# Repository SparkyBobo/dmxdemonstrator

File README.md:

# DMX Demonstrator

## Background

When I was in grad school, I was challenged by my technical theater professor to create a device to demonstrate DMX. What we devised was a transmitter receiver pair with 4 controls and 4 dimmers and the pair was linked by a three-wire cable. The transmitter had a fixed clock that could run at reasonable fast, xxkHz, and a variable clock that could be adjusted down to 0.5 hZ. By switching back and forth, you could toggle between "real-time" updates and a slow pace that can be used to see each bit on the wire. We then built a lecture around how the data was digitized, serialized, de-serialized, and converted back to analog to control the dimmers.

The device was built and did function even though it failed to follow a number of best engineering practices. At that time, we didn't have [GitHub](https://github.com/) and [Tindie](https://www.tindie.com/) so sharing the project was by word-of-mouth and email; yes, we did have [email](https://en.wikipedia.org/wiki/Email). Only one other group considered building a replica but alas they never did. The device was built only once and transported to a USITT conference in Las Vegas, where the EPROM failed and we had nothing to show except a presentation. Only a handful of students at my school ever got to see it function.

That was 25 years ago. For it's anniversary, I've decided to revive the project and build 2 new implementations. The first is based on Arduino for a cheap but functional version of the project that is unlikely to fail or break the bank. The second is an updated recreation of the original using today's available hardware but without deviating from the original TTL-based design, i.e. no microprocessors or microcontrollers. I'll admit this last one is really just for me because I love designing electronics, drawing schematics, laying out PCBs, and assembling electronics.

## Hardware

In the hardware folder, you'll find a series of designs:

- transmitter - An arduino-based transmitter.
- receiver - An arduino-based receiver.
- control-pro - A controller built to work with either transmitter or transmitter-pro.
- constant voltage display driver - An external large-format display for data and clock signals.

## Firmware/Software

As you would expect, the Arduino-based version is implemented mostly in software. The Sketch files for both transmitter and receiver are in the software folder and ready to upload to an Arduino UNO R3. The sketch and hardware will likely work with any Arduino-compatible board.

## Monitoring

All informational output is sent to via the serial port for easy display on a computer. However, the clock and serial data are displayed via LEDs to visualize the serial data.

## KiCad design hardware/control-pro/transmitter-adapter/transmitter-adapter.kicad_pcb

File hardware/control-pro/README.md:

# DMX Demonstrator Control Pro  (DMX-CP*)

## Overview

The Control Pro is built to work with either transmitter or transmitter-retro. When used with an Arduino, an additional board, the Transmitter IO Interface (DMX-TX2), is required to connect the Control Pro to the Arduino. The transmitter software automatically detects whether DMX-TX1, the standard transmitter, or DMX-TX2, the Transmitter IO Interface, is connected.

The Control Pro is designed so that a series of components are sandwiched between 2 circuit boards. As a result, the heights of the components are fairly sensitive in order to make things line up nicely. The DMX-CPDB and DMX-CPCB boards contains all the parts and are the bottom of the sandwich, the DMX-CPDF and DMX-CPCB are the faceplate, i.e. the tops of the sandwich. If you are wondering why there are 4 total boards, see _PCB->Quality vs Price_ below.

## Online parts list

For a complete list of parts, see:

- [Clock Control Bill of materials](clock-control/clock-control.bom.md), [Clock Control Parts](clock-control/clock-control.parts.md)
- [Dimmer Control Bill of materials](dimmer-control/dimmer-control.bom.md), [Dimmer Control Parts](dimmer-control/dimmer-control.parts.md)
- [Clock Faceplate Bill of materials](clock-faceplate/clock-faceplate.bom.md), [Clock Faceplate Parts](clock-faceplate/clock-faceplate.parts.md)
- [Dimmer Faceplate Bill of materials](dimmer-faceplate/dimmer-faceplate.bom.md), [Dimmer Faceplate Parts](dimmer-faceplate/dimmer-faceplate.parts.md)
- [Transmitter Adapter Bill of materials](transmitter-adapter/transmitter-adapter.bom.md), [Transmitter Adapter Parts](transmitter-adapter/transmitter-adapter.parts.md)

You can also buy some of the parts for the Control Pro online from a Wishlist:

- Sparkfun: [Common](https://www.sparkfun.com/wish_lists/160406), [DMX-CP*](https://www.sparkfun.com/wish_lists/160543)
- Adafruit: [Common](http://www.adafruit.com/wishlists/589832), [DMX-CP*](http://www.adafruit.com/wishlists/590129)

Sparkfun's rainbow LED pack only include 2 sets of color so if you are building more than 2 transmitters or receivers, make sure to buy 1 pack for every 2 transmitters/receivers. Adafruit's LED pack includes 5 sets of each color.

## PCB

You can order the PCBs from [OHS Park](https://oshpark.com/):

- [Clock Control: DMX-CPCB, Rev 1.3](https://oshpark.com/shared_projects/llBuRZd8)
- [Clock Faceplate: DMX-CPCF, Rev 1.3](https://oshpark.com/shared_projects/S9LARHyr)
- [Dimmer Control: DMX-CPDB, Rev 1.3](https://oshpark.com/shared_projects/O76YiRT8)
- [Dimmer Faceplate: DMX-CPDF, Rev 1.3](https://oshpark.com/shared_projects/bZqKigQF)
- [Transmitter Adapter: DMX-CPAD, Rev 1.3](https://oshpark.com/shared_projects/xCkM6ON9)

You can read more about ordering pcbs [here](../pcb.md).

## Assembly Notes

The Control Pro is designed so that a series of components are sandwiched between 2 circuit boards. As a result, the heights of the components are fairly sensitive in order to make things line up nicely. Here are the parts for which I designed. The DMX-CPDB and DMX-CPCB boards contains all the parts and are the bottom of the sandwich, the DMX-CPDF and DMX-CPCB are the faceplate, i.e. the tops of the sandwich. If you are wondering why there are 4 total boards, [read this](../pcb.md).

### Slider Potentiometers

Getting a potentiometer and knob combo that would work with the rest of the components was probably the hardest part of part selection.
I had initially ordered some 60mm 10k sliders from SparkFun with matching knobs and they measures about 25mm from the bottom of the
part to the bottom of the knob, which is way too tall for the other components! I landed on a combination of Bourns PTA Series
sliders with an knob available from Sparkfun (and others). During this process, I opted for a 45mm travel to keep the board smaller/cheaper
while still offering good mechanical resolution. The specific parts I designed for are:

- Dimmer Sliders: Bournes PTA4543-2015DPB103, quantity 4:

  - [Data sheet](https://www.mouser.com/datasheet/2/54/pta-778345.pdf)
  - [Digikey PTA4543-2015DPB103-ND](https://www.digikey.com/products/en?keywords=PTA4543-2015DPB103-ND)
  - [Mouser 652-PTA45432015DPB10](https://www.mouser.com/ProductDetail/Bourns/PTA4543-2015DPB103?qs=U%2FacTlguYxbmwS%2FtylIWJw%3D%3D)

- Knobs: Eagle 450-3051, quantity 4:

  - [Datasheet](https://www.mouser.com/datasheet/2/209/EPD-200140-1171100.pdf)
  - [Mouser 450-3051](https://www.mouser.com/ProductDetail/Eagle-Plastic-Devices/450-3051?qs=hTs5c5NaUrTeABpuQnP9ug%3D%3D)
  - [Sparkfun COM-09120](https://www.sparkfun.com/products/9120) - Included in online parts list

### Toggle Switches

Just about any miniature toggle switch will do, many manufacturers make a switch in a similar size. I specifically used the E-Switch Series 100 Miniature Toggle Switches, specifically:

- Clock Speed: E-Switch 100DP3T1B1M1QEH, quantity 1:

  - [Datasheet](https://sten-eswitch-13110800-production.s3.amazonaws.com/system/asset/product_line/data_sheet/129/100.pdf)
  - [Digikey EG2413-ND](https://www.digikey.com/products/en?keywords=100DP3T1B1M1QEH)
  - [Mouser 612-100-H1111](https://www.mouser.com/ProductDetail/E-Switch/100DP3T1B1M1QEH?qs=g8hxKYs5b3yy1L1GZVrx5w%3D%3D)

- Clock Step: E-Switch 100SP2T1B1M1QEH, quantity 1:

  - [Datasheet](https://sten-eswitch-13110800-production.s3.amazonaws.com/system/asset/product_line/data_sheet/129/100.pdf)
  - [Digikey EG2373-ND](https://www.digikey.com/product-detail/en/e-switch/100SP2T1B1M1QEH/EG2373-ND/378842)
  - [Mouser 612-100-B1111](https://www.mouser.com/ProductDetail/E-Switch/100SP2T1B1M1QEH?qs=HKd%2Fp3M7KlWCZ%252BGqDexPKQ%3D%3D)

### Rotary Potentiometer

With the toggle and sliders determining the basic component height, I searched for a rotary potentiometer to fit the requirements and once again found a Bournes product. It has a 6mm "D"/flattened shaft so just about any 6mm flattened shaft knob will work but something with a set screw will help secure it. I did not find a great choice at Digikey or Mouser but Amazon and EBay has a ton of choices, designed for use with musical instruments.

Sparkfun offers a potentiometer and knob that make an excellent choice. The knob even [goes to 11](https://en.wikipedia.org/wiki/Up_to_eleven). The Sparkfun part is not a Bournes PTV09A-4030F-B103 but it's the same physical size and resistance.

Specifically:

- Clock Speed Control: Bournes PTV09A-4030F-B103, quantity 1:

  - [Datasheet](https://www.bourns.com/docs/Product-Datasheets/PTV09.pdf)
  - [Digikey 118-PTV09A-4030F-B103-ND](https://www.digikey.com/en/products/detail/bourns-inc/PTV09A-4030F-B103/3820581)
  - [Mouser 652-PTV09A-4030FB103](https://www.mouser.com/ProductDetail/Bourns/PTV09A-4030F-B103?qs=Zq5ylnUbLm4pfFuWlwC80Q%3D%3D)
  - [Sparkfun COM-09288](https://www.sparkfun.com/products/9288) - Included in online parts list

- Knob, quantity 1:

  - [Sparkfun COM-11951](https://www.sparkfun.com/products/11951) - Included in online parts list
  - [Adafruit 5527](https://www.adafruit.com/product/5527) - Included in online parts list

### LEDs and Spacers

Luckily most LEDs have leads long enough to make it from the bottom to top board so nothing special is needed here, just make sure to have 17.5mm of lead length. Most LEDs have a voltage and current range near 2v and 10ma and the design will accommodate variances easily.

I like the [Sparkfun rainbow LED Kit](https://www.sparkfun.com/products/12903) which gives you 2 each of 6 colors, letting you match colors for dimmers 1-4, data and clock on both the transmitter and receiver without re-using colors. This LED kit is included in the common parts list. However, they will need a bit of added stability, which is where an LED spacer is needed. Something between 16mm and 17mm will work fine. Here's a suitable one:

- LED: T1 3/4 or 5mm Led in various colors, quantity 1:

  - [Sparkfun rainbow LED Kit](https://www.sparkfun.com/products/12903) - Included in common online parts list
  - [Adafruit Multicolor LED Kit](https://www.adafruit.com/product/4203) - Included in common online parts list

- LED Spacer: Würth 705820170, quantity 6:

  - [Data sheet](https://www.we-online.de/katalog/datasheet/705820xxx_overview.pdf)
  - [Digikey 732-11617-ND](https://www.digikey.com/product-detail/en/w%C3%BCrth-elektronik/705820170/732-11617-ND/7681962)
  - [Mouser 710-705820170](https://www.mouser.com/ProductDetail/Wurth-Elektronik/705820170?qs=wr8lucFkNMUaK6Cwpwjx5Q%3D%3D)

### Cable and Connector

To connect the controller to the transmitter, you'll need some cables and connectors. Ribbon cable makes a nice choice for this and you can find pre-made ribbon cable assemblies on Amazon and EBay easily. I've designed for a 16 pin cable. I recommend shrouded headers for connecting to PCBs and it ensures you don't plug the cable in backwards. Here are some suitable headers:

- Header, horizontal: Würth Elektronik 61201621721, quantity 5:

  - [Datasheet](https://www.we-online.com/components/products/datasheet/61201621721.pdf)
  - [Digikey 732-2099-ND](https://www.digikey.com/en/products/detail/w%C3%BCrth-elektronik/61201621721/2060595)
  - [Mouser 710-61201621721](https://www.mouser.com/ProductDetail/Wurth-Elektronik/61201621721?qs=ZtY9WdtwX56ShT0tAQh3qw%3D%3D)

- Cable, quantity 2:

  - [Amazon: Antrader 30CM 16-Pin IDC Connector Flat Ribbon Cable](https://smile.amazon.com/dp/B07FZWH9S6/ref=cm_sw_em_r_mt_dp_n0-BFbMSE9MJX )

### Standoff and Feet

Finally, you'll need some standoffs to hold the boards together and some feet to avoid the bottom PCB from dragging across the table. You can adjust the screw size and add some washers or plexiglass if you like to create a smooth bottom surface. The standoffs should be 18mm in length and the boards are designed for an M3 screw. Amazon and EBay offer tons of options. I even found [purple ones on EBay](https://www.ebay.com/itm/M3-Aluminum-Alloy-Female-Hex-Hexagon-Threaded-Bush-Sleeve-Standoff-Pillar-Spacer/174350100853?ssPageName=STRK%3AMEBIDX%3AIT&var=473550930125&_trksid=p2060353.m1438.l2649).

- Standoff: Keystone 24476/24446/25531 (M3, 18mm length), quantity 4:

  - [Digikey 36-24446-ND, aluminum](https://www.digikey.com/product-detail/en/keystone-electronics/24446/36-24446-ND/1532945)
  - [Mouser 534-24436, aluminum](https://www.mouser.com/ProductDetail/Keystone-Electronics/24436?qs=UWqYQ%2F2cZWv7%252B7DoeljlhQ%3D%3D)
  - [Ebay M3 Aluminum Alloy Red, Blue, Purple, Black, Gold, Silver](https://www.ebay.com/itm/M3-Aluminum-Alloy-Female-Hex-Hexagon-Threaded-Bush-Sleeve-Standoff-Pillar-Spacer/174350100853?ssPageName=STRK%3AMEBIDX%3AIT&var=473550930125&_trksid=p2060353.m1438.l2649)

### Passive components

The Control Pro has a few passive listed on the schematic and are included in the common parts lists:

- Sparkfun: [Common](https://www.sparkfun.com/wish_lists/160406)
- Adafruit: [Common](http://www.adafruit.com/wishlists/589832)

## Version History

### Rev 1.3

- Add copper pours to both faceplates
- No changes to control boards.
- Added transmitter adapter.

### Rev 1.2

#### DMX-CPC*

- Split clock controls out to its own PCB
- Added 2nd 16 pin connector to daisy chain with DMX-CPD*.
- Switched to horizontal 16 pin connectors since vertical was too tall with a cable plugged in
- Swapped the clock speed and step switches to match the order on the TX1
- Swapped the data and clock LEDs to match the order on the TX1

#### DMX-CPD*

- Split dimmer controls out to its own PCB
- Added 2nd 16 pin connector to daisy chain with DMX-CPC*.
- Switched to horizontal 16 pin connectors since vertical was too tall with a cable plugged in

### Rev 1.1

#### DMX-CPB

- Added rounded corners.

#### DMX-CPF

- Removed copper from 3rd slider slot by enlarging slot width.
- Added rounded corners.

### Rev 1.0

- Initial draft, all boards.

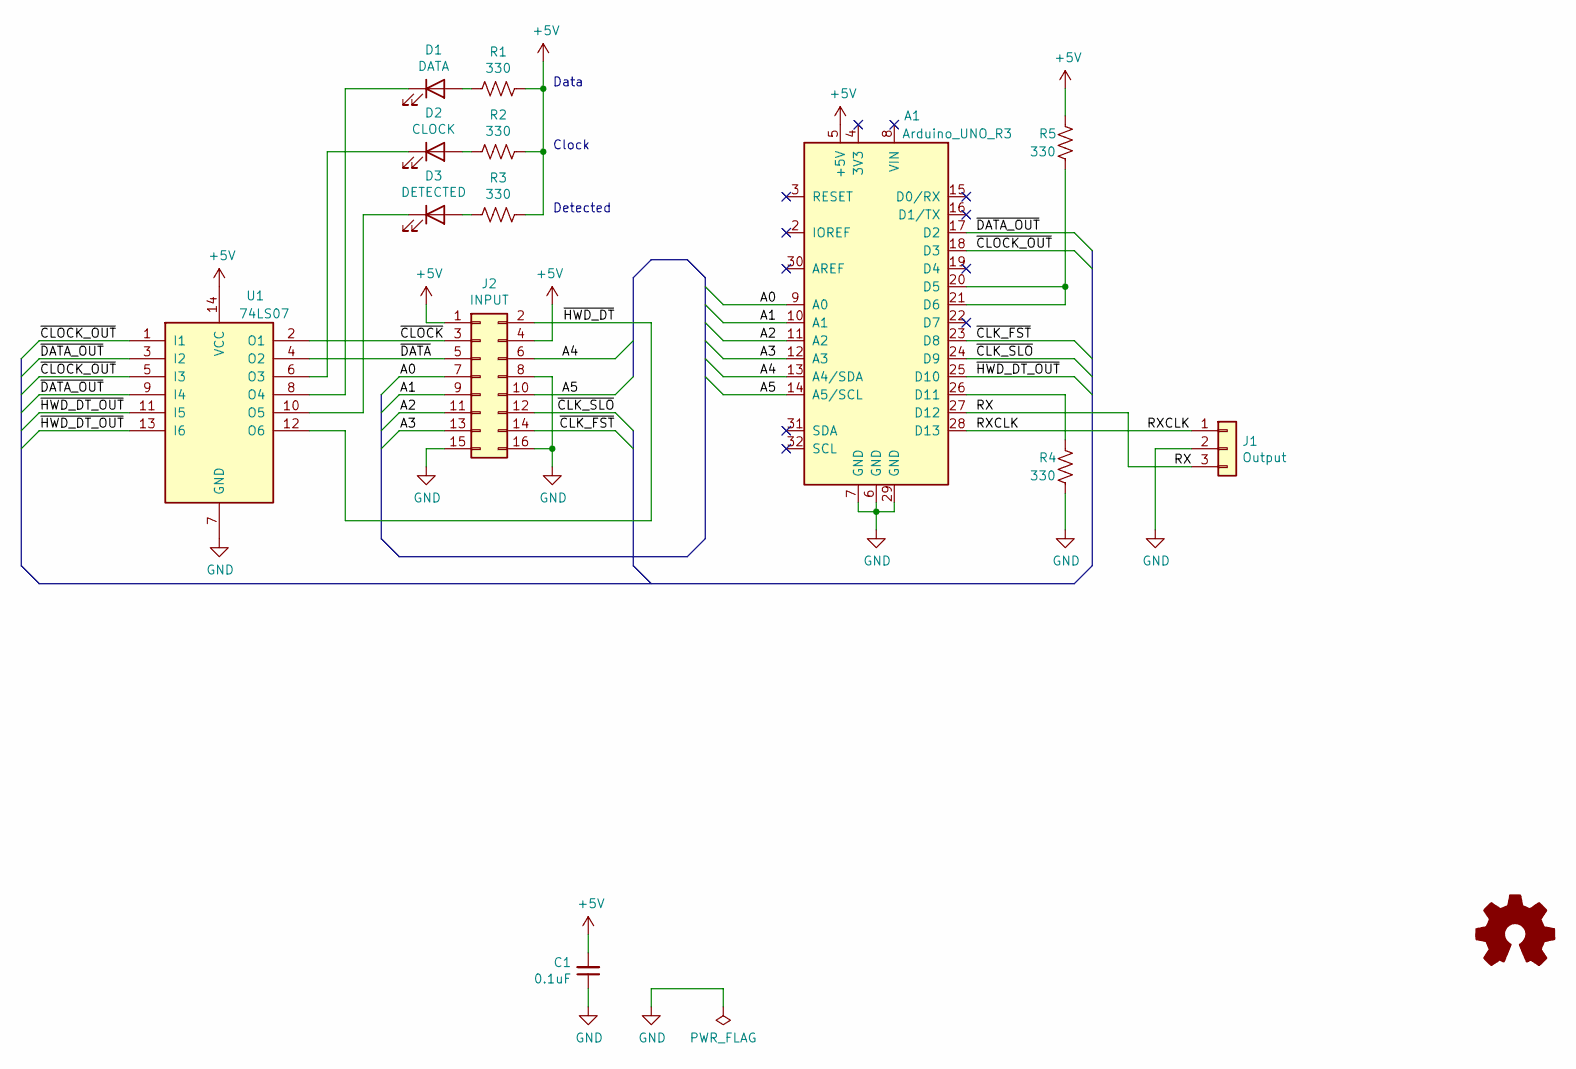
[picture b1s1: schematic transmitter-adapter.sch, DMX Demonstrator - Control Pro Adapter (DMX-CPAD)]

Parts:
A1: Arduino_UNO_R3; ARDUINO_R3_NO_HOLES; PartId A_ARDUINO,H_ARDUINO
C1: 0.1uF; C_Disc_D3.0mm_W1.6mm_P2.50mm; PartId C_DECOUPLE
D1: DATA; LED_D5.0mm; PartId LED_GRN
D2: CLOCK; LED_D5.0mm; PartId LED_RED
D3: DETECTED; LED_D5.0mm; PartId LED_RED
J1: Output; PinHeader_1x03_P2.54mm_Horizontal; PartId H_1x3_RA
J2: INPUT; IDC-Header_2x08_P2.54mm_Horizontal; PartId H_CPRO_RA
R1, R2, R3, R4, R5: 330; R_Axial_DIN0207_L6.3mm_D2.5mm_P10.16mm_Horizontal; PartId R_LED
U1: 74LS07; DIP-14_W7.62mm; PartId U_74LS07

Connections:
+5V: A1.5 (+5V), C1.2, J2.1, J2.4, R1.1, R2.1, R3.1, R5.1, U1.14 (VCC)
/A0: A1.9 (A0), J2.7
/A1: A1.10 (A1), J2.9
/A2: A1.11 (A2), J2.11
/A3: A1.12 (A3), J2.13
/A4: A1.13 (A4/SDA), J2.6
/A5: A1.14 (A5/SCL), J2.10
/RX: A1.27 (D12), J1.3
/RXCLK: A1.28 (D13), J1.1
/~CLK_FST: A1.23 (D8), J2.14
/~CLK_SLO: A1.24 (D9), J2.12
/~CLOCK: J2.3, U1.2 (O1)
/~CLOCK_OUT: A1.18 (D3), U1.1 (I1), U1.5 (I3)
/~DATA: J2.5, U1.4 (O2)
/~DATA_OUT: A1.17 (D2), U1.3 (I2), U1.9 (I4)
/~HWD_DT: J2.2, U1.12 (O6)
/~HWD_DT_OUT: A1.25 (D10), U1.11 (I5), U1.13 (I6)
GND: A1.6 (GND), A1.7 (GND), A1.29 (GND), C1.1, J1.2, J2.8, J2.15, J2.16, R4.2, U1.7 (GND)
unnamed: A1.20 (D5), A1.21 (D6), R5.2
unnamed: A1.26 (D11), R4.1
unnamed: D1.1 (K), U1.8 (O4)
unnamed: D1.2 (A), R1.2
unnamed: D2.1 (K), U1.6 (O3)
unnamed: D2.2 (A), R2.2
unnamed: D3.1 (K), U1.10 (O5)
unnamed: D3.2 (A), R3.2

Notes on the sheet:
Clock
Data
Detected

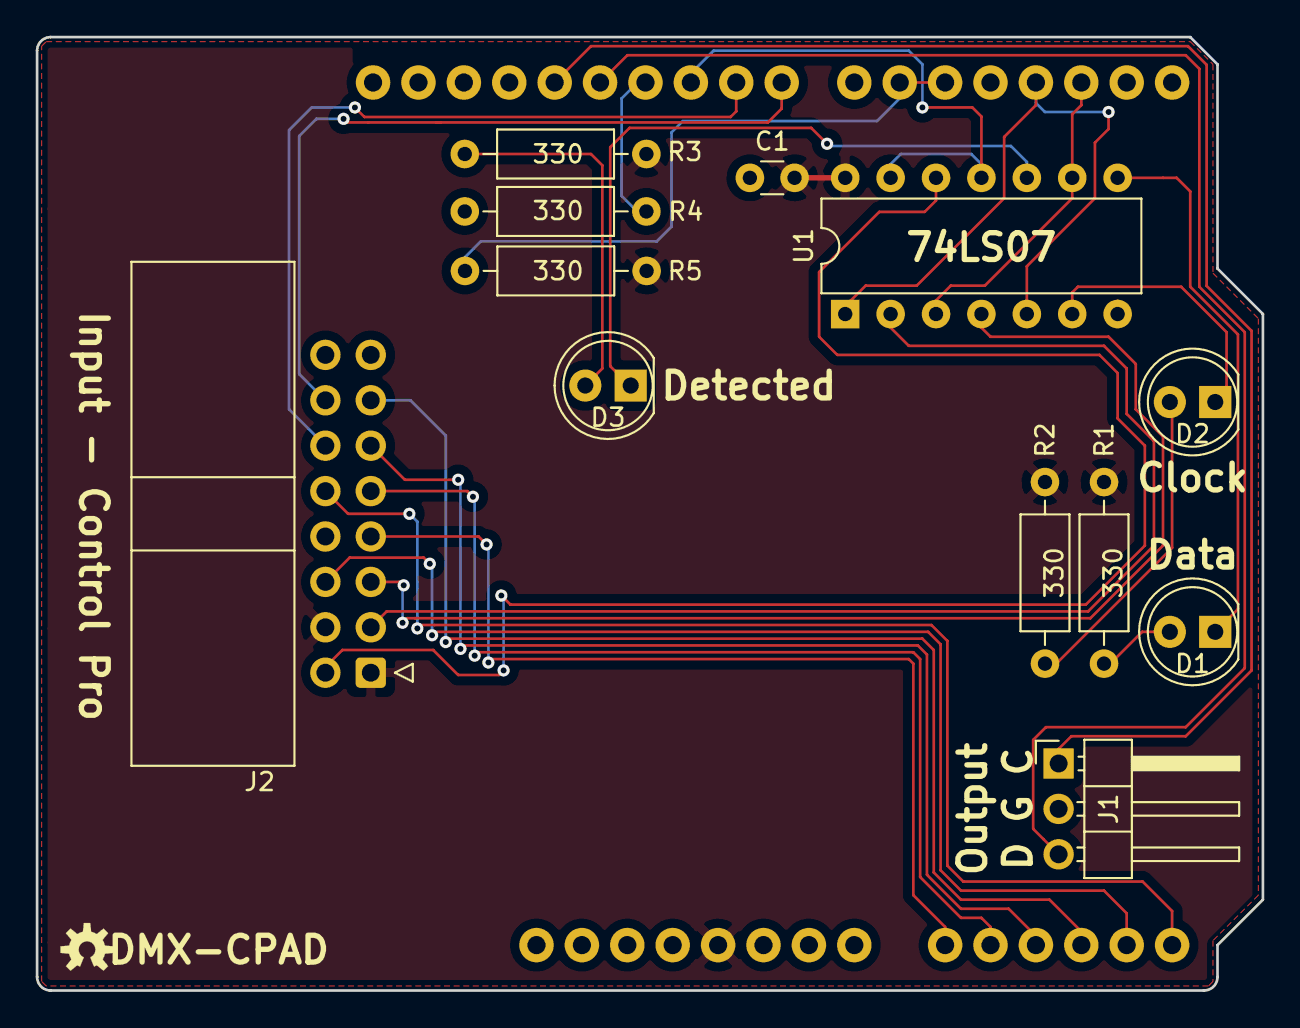
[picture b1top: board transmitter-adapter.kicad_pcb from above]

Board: 2 copper layers, 68.6 x 53.3 mm, 13 parts (0 on the bottom side), 26 nets.

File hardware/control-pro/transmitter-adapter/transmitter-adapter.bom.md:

# Bill Of Materials (BOM)

## Schematic

**Filename:** E:\OpenSource\dmxdemonstrator\hardware\control-pro\transmitter-adapter\transmitter-adapter.sch

**Date Modified:** 5/25/2024 12:26:10 AM

**Kicad Version:** Eeschema (5.1.12)-1

**Component Count:** 13

## Components

Item#|Quantity|Reference|Description|Manufacturer|Part Number|Datasheet|Notes
-----|--------|---------|-----------|------------|-----------|---------|-----
1|1|PCB|Control-Pro Adapter PCB|OHSPark|DMX-CPAD, Rev 1.3||[Order](https://oshpark.com/shared_projects/xCkM6ON9)|
2|1|A1|Arduino UNO/Leonardo|||[Data Sheet](https://www.arduino.cc/en/Main/arduinoBoardUno)|
3|1|A1|Arduino R3 Headers|||[Data Sheet](https://www.arduino.cc/en/Main/arduinoBoardUno)|
4|1|C1|0.1uF||||
5|1|D1|Green LED, 5mm||||
6|1|D2|Red LED, 5mm||||
7|1|D3|Red LED, 5mm||||
8|1|J1|3-pin right-angle header||||
9|1|J2|2x8 shrouded right-angle header|Wurth Elektronik|61201621721|[Data Sheet](https://www.we-online.com/components/products/datasheet/6120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|
10|5|R1, R2, R3, R4, R5|330 ohm||||
11|1|U1|74LS07|Texas Instruments|SN74LS07N|[Data Sheet](https://www.ti.com/lit/gpn/sn74ls07)|
<!--BOMROW-->

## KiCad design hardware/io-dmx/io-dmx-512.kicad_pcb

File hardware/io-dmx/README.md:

# DMX Demonstrator DMX-512 IO Module (DMX-IO1)

## Overview

The DMX-512 IO Module is a stand-alone module which generates or receives a DMX-512 signal, allowing the DMS Demonstrator system to communicate with DMX-512-compatible equipment. It can be used with a Receiver (DMX-RX2) to receive or re-transmit DMX-512. It can also be used with a Transmitter (DMX-TX2) to transmit the data stream to DMX-512.

## Online parts list

For a complete list of parts, see:

- [Bill of materials](io-dmx-512.bom.md)
- [Part lists](io-dmx-512.parts.md)

Sadly, Sparkfun and Adafruit do not offer all of the components required for DMX-512 IO Module. Additionally, Digikey does not carry Neutrik for connecting to the DMX devices. The parts can be purchased from [Mouser](https://www.mouser.com/) or [Newark](https://www.newark.com/). Some parts can be purchased from [SparkFun](https://www.sparkfun.com/) and [Adafruit](https://www.adafruit.com/).

### Required components

- U5, MAX485E

  - [MAX485E Data Sheet](https://www.analog.com/media/en/technical-documentation/data-sheets/MAX1487E-MAX491E.pdf)
  - [Mouser 700-MAX485CPA](https://www.mouser.com/ProductDetail/Analog-Devices-Maxim-Integrated/MAX485CPA%2b?qs=1THa7WoU59FcxPgOoQv70A%3D%3D)
  - [Newark 881Y9485](https://www.newark.com/analog-devices/max485cpa/rs422-rs485-transceiver-2-5mbps/dp/81Y9485?ost=max485cpa)

- C5, 0.1uF

  - [SparkFun 8375](https://www.sparkfun.com/products/8375)
  - [Adafruit 753](https://www.adafruit.com/product/753)
  - [Mouser 80-C320C104K5R7301](https://www.mouser.com/ProductDetail/KEMET/C320C104K5R5TA7301/?qs=cWONFOU2MXytiO%2Fz22pl%252Bg%3D%3D)
  - [Newark 13K6284](https://www.newark.com/kemet/c315c104m5u5ta/capacitor-mlcc-z5u-100nf-50v-radial/dp/39K6432)

- R2, R5, and R7, 470 ohm

  - [Adafruit 2781](https://www.adafruit.com/product/2781)
  - [Mouser 603-CFR-25JT-52-470R](https://www.mouser.com/ProductDetail/Yageo/CFR-25JT-52-470R/?qs=sGAEpiMZZMtlubZbdhIBIFoOGUvNp40adtovOrQ4BzA%3D)
  - [Newark 38K0375](https://www.newark.com/multicomp-pro/mcf-0-25w-470r/carbon-film-resistor-470-ohm-250mw/dp/38K0375)

- J1, 2x7 shrouded right-angle header

  - [Datasheet](https://www.we-online.com/components/products/datasheet/61201421721.pdf)
  - [Mouser 710-61201421721](https://www.mouser.com/ProductDetail/Wurth-Elektronik/61201421721?qs=PhR8RmCirEbQk5OcjPFu0A%3D%3D)
  - [Newark 75AJ1395](https://www.newark.com/wurth-elektronik/612014235221/conn-r-a-header-14pos-2row-2-54mm/dp/75AJ1395)

### DMX Connectors

DMX commonly uses a 5-pin XLR connector. From the [Recommended Practices for DMX-512, 2nd Edition by Adam Bennette](https://tsp.esta.org/tsp/documents/docs/DMX512-A_Guide_(8x10)_ESTA.PDF):

> DMX512-A lines connect with equipment via XLR 5 pin type connectors. A female connector is fitted to a transmitter and a male connector to a receiver.

However, some DMX equipment is equipped 3-pin XLR connectors which does not comply with the USITT spec. That said, the DMX-IO1 supports both XLR-5 and XLR-3 connectors, one male and one female. The design is made for Neutrik connectors (which is not a brand that Digikey carries). There are a few variation of the basic part numbers listed below with different shielding configurations. For instance, Newark only carries the NC3FAH-2, which works fine in place of the NC3FAH.

- XLR, 5-pin male

  - [NC5MAH Datasheet](https://www.neutrik.com/en/product/nc5mah.pdf)
  - [Mouser 568-NC5MAH](https://www.mouser.com/ProductDetail/Neutrik/NC5MAH/?qs=43pPWqpsSNtpdAMzqMXlkw%3D%3D)
  - [Newark 25C4313](https://www.newark.com/neutrik/nc5mah/connector-xlr-audio-plug-5pos/dp/25C4313?ost=nc5mah)

- XLR, 5-pin female

  - [NC5FAH Datasheet](https://www.neutrik.com/en/product/nc5fah.pdf)
  - [Mouser 568-NC5FAH](https://www.mouser.com/ProductDetail/Neutrik/NC5FAH/?qs=JfNPhaIww3Jo8umm7Mfi2w%3D%3D)
  - [Newark 94C1524](https://www.newark.com/neutrik/nc5fah/connector-xlr-receptacle-5-position/dp/94C1524?ost=nc5fah)

- XLR, 3-pin male

  - [NC3MAH Datasheet](https://www.neutrik.com/en/product/nc3mah.pdf)
  - [Mouser 568-NC3MAH](https://www.mouser.com/ProductDetail/Neutrik/NC3MAH/?qs=MO8z%252B%252BLepAHrH1t47qrfbA%3D%3D)
  - [Newark 91F3468](https://www.newark.com/neutrik/nc3mah/connector-xlr-plug-3-position/dp/91F3468?st=nc3mah)

- XLR, 3-pin female

  - [NC3FAH-0 Datasheet](https://www.neutrik.com/en/product/nc3fah-0.pdf)
  - [Mouser 568-NC3FAH](https://www.mouser.com/ProductDetail/Neutrik/NC3FAH/?qs=43pPWqpsSNse2FCN7qQVQw%3D%3D)
  - [Newark 27B4208](https://www.newark.com/neutrik/nc3fah2/connector-xlr-audio-rcpt-3pos/dp/27B4208)

### DMX Termination

From the [Recommended Practices...](https://tsp.esta.org/tsp/documents/docs/DMX512-A_Guide_(8x10)_ESTA.PDF):

> Incorrect or missing termination is probably the single most common reason for faulty DMX512-A systems. The terminator is a resistor fitted between the two data lines (pins 2 & 3 of an XLR 5 pin connector) at the end of the cable furthest from the transmitter.

The DMX-IO1 includes a part to terminate the DMX-512 line. To add termination, populate R1 with a 120 ohm resistor. Add SW1 to make termination selectable or solder a jumper between the two round pads for permanent termination.

- R1 - 120 ohm

  - [Mouser 603-CFR-25JT-52-120R](https://www.mouser.com/ProductDetail/Yageo/CFR-25JT-52-120R/?qs=sGAEpiMZZMtlubZbdhIBIFoOGUvNp40ae6q2awCfJoc%3D)
  - [Newark 38K0333](https://www.newark.com/multicomp-pro/mcf-0-25w-120r/carbon-film-resistor-120-ohm-250mw/dp/38K0333)

- SW1 - slide switch SPDT

  - [Data Sheet](https://www.mouser.com/datasheet/2/140/EG-3305192.pdf)
  - [Sparkfun COM-00102](https://www.sparkfun.com/products/102)
  - [Adafruit 805](https://www.adafruit.com/product/805)
  - [Mouser 612-EG1218](https://www.mouser.com/ProductDetail/E-Switch/EG1218?qs=xDsBkp9LkocT0c8K%252B5e%2FgA%3D%3D)|
  - [Newark 15N7301](https://www.newark.com/e-switch/eg1218/slide-switch-spdt-200ma/dp/15N7301?st=eg1218)

### Isolation

From the [Recommended Practices...](https://tsp.esta.org/tsp/documents/docs/DMX512-A_Guide_(8x10)_ESTA.PDF):

> The solution to the grounding problems described above is to disconnect the receiver ground from the DMX512-A line ground / 0V wire, by means of an optical isolation circuit.

The DMX-IO1 shamelessly steals it's isolation design from [SparkFun ESP32 Thing Plus DMX to LED Shield](https://www.sparkfun.com/products/15110) which implements isolation including power supply isolation. Isolation is implemented using the following parts:

- U1, RFM-0505S

  - [RFM-0505S Datasheet](https://recom-power.com/pdf/Econoline/RFM.pdf)
  - [Mouser 5919-RFM-0505S](https://mou.sr/3UqOlN3)
  - [Newark 54AC6727](https://www.newark.com/recom-power/rfm-0505s/dc-dc-converter-5v-0-2a/dp/54AC6727)

- U2-U4, 6N137

  - [6N137 Datasheet](https://www.mouser.com/datasheet/2/427/6n137-1767489.pdf)
  - [Mouser 782-6N137](https://www.mouser.com/ProductDetail/Vishay-Semiconductors/6N137/?qs=xCMk%252BIHWTZMrQz4FyDXhMg%3D%3D)
  - [Newark 52M1895](https://www.newark.com/vishay/6n137/optocoupler-transistor-5300vrms/dp/52M1895?st=6n137)

- C2-C4, 0.1uF

  - [SparkFun 8375](https://www.sparkfun.com/products/8375)
  - [Adafruit 753](https://www.adafruit.com/product/753)
  - [Mouser 80-C320C104K5R7301](https://www.mouser.com/ProductDetail/KEMET/C320C104K5R5TA7301/?qs=cWONFOU2MXytiO%2Fz22pl%252Bg%3D%3D)
  - [Newark 13K6284](https://www.newark.com/kemet/c315c104m5u5ta/capacitor-mlcc-z5u-100nf-50v-radial/dp/39K6432)

- R3, R4, and R6, 470 ohm

  - [Adafruit 2781](https://www.adafruit.com/product/2781)
  - [Mouser 603-CFR-25JT-52-470R](https://www.mouser.com/ProductDetail/Yageo/CFR-25JT-52-470R/?qs=sGAEpiMZZMtlubZbdhIBIFoOGUvNp40adtovOrQ4BzA%3D)
  - [Newark 38K0375](https://www.newark.com/multicomp-pro/mcf-0-25w-470r/carbon-film-resistor-470-ohm-250mw/dp/38K0375)

You can use the DMX-IO1 without isolation by leaving out these parts (saving about $12 USD) and installing 5 solder bridges to bypass the isolation circuits:

- Omit U1
- Under U1, connect pins 1 and 4 to bypass +5v
- Under U1, connect pins 2 and 3 to bypass GND
- Omit U2
- Under U2, solder JP1 closed to bypass RX
- Omit U3
- Under U3, solder JP2 closed to bypass DIR
- Omit U4
- Under U4, solder JP3 closed to bypass TX
- Omit C2
- Omit C3
- Omit C4
- Omit R3
- Omit R4
- Omit R6

## PCB

You can order the PCBs from [OHS Park](https://oshpark.com/):

- [DMX-IO1, Rev 1.7](https://oshpark.com/shared_projects/jqZlCb1q)

You can read more about ordering pcbs [here](..\pcb.md).

## Version History

### Rev 1.7

- Fix pinout of U1

### Rev 1.6

- Added termination switch
- Change to RFM-0505S
- Change to MAX485E
- Swap A and B on Max485
- Avoid split power planes under WH4
- Remove pads from XLR alignment pins

### Rev 1.5

- Move R5 to make room for R2 silkscreen
- Move R1 to make room for DMX connector

### Rev 1.4

- Fix issue with DMX A and B being reversed
- Group bypass-only resistors together
- Add ISO bypass solder bridges
- Add silkscreen values
- Remove RDM bias resistors

### Rev 1.3

- Remove isolation bypass artifacts from schematic and board, moved to docs only.
- Remove RDM line biasing since the isolation circuit does not support RDM.

### Rev 1.2

- Switched to a stand-alone module

### Rev 1.1

- Moved DMX connectors
- Added bypass pads to U1

### Rev 1.0

- Initial draft

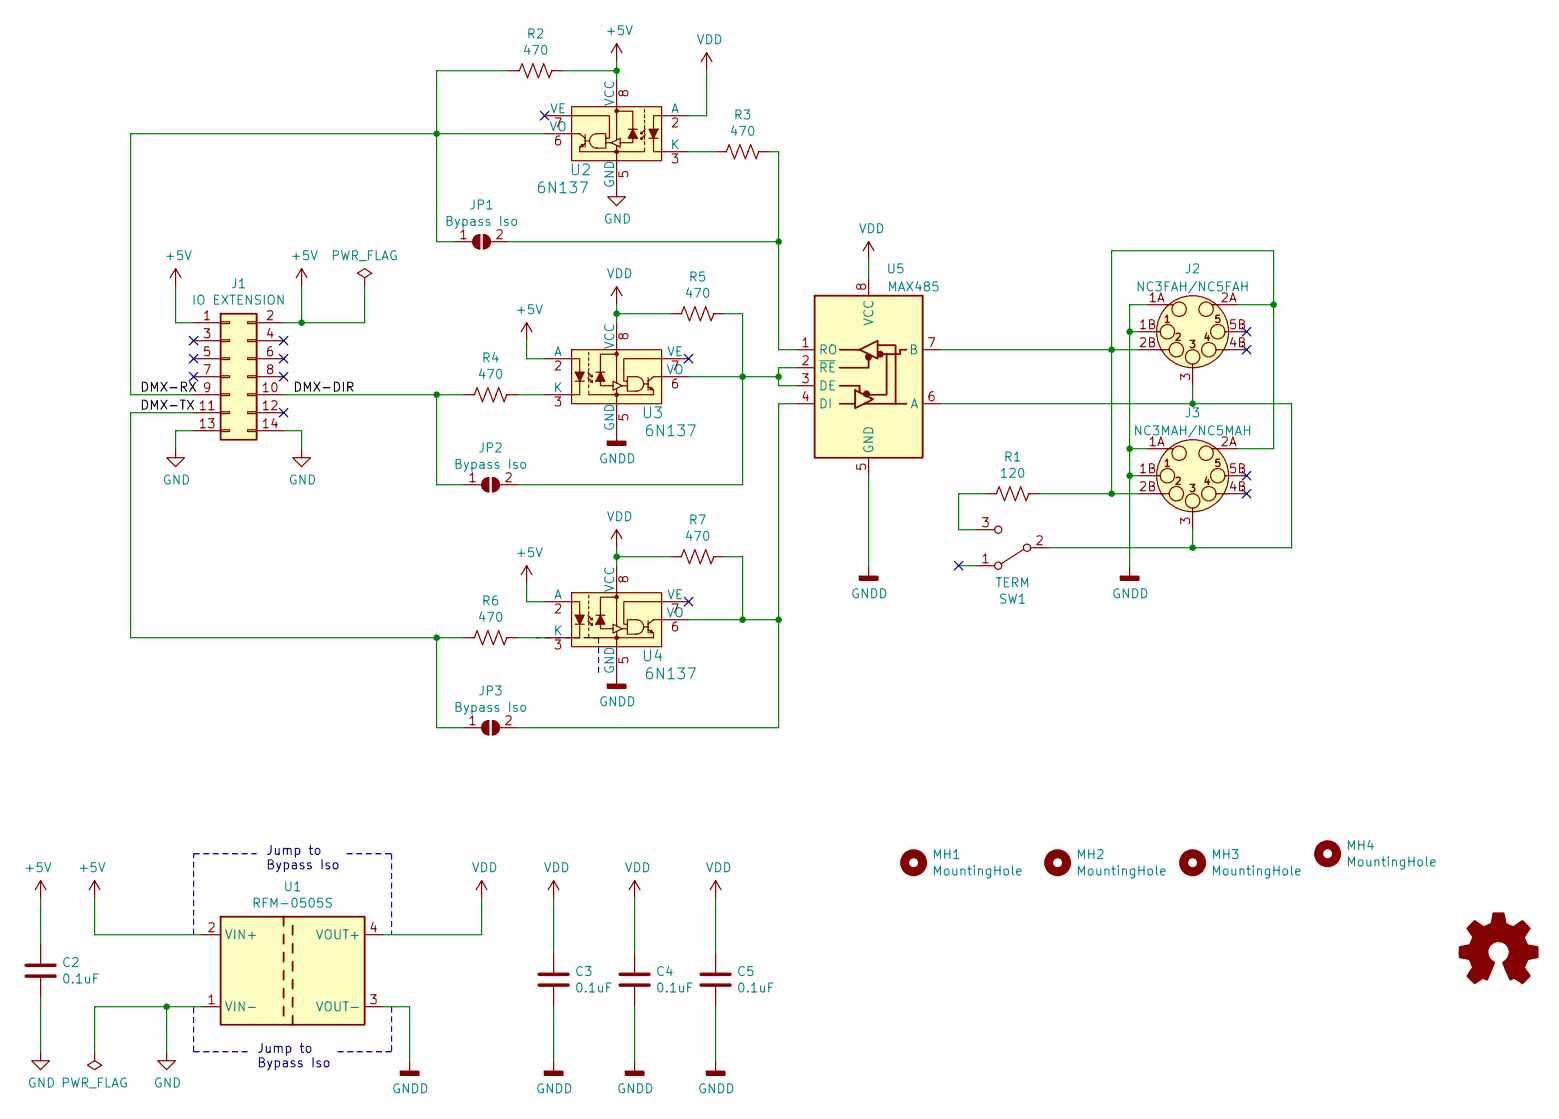
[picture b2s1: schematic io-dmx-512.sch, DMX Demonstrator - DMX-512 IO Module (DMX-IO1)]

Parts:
C2, C3, C4, C5: 0.1uF; C_Rect_L4.6mm_W2.0mm_P2.50mm_MKS02_FKP02; PartId C_DECOUPLE
J1: IO EXTENSION; IDC-Header_2x07_P2.54mm_Horizontal; PartId H_IO_RA,JP_IO
J2: NC3FAH/NC5FAH; NEUTRIK-NC3FAH-NC5FAH; PartId J_XLR5F
J3: NC3MAH/NC5MAH; NEUTRIK-NC3MAH-NC5MAH; PartId J_XLR5M
JP1, JP2, JP3: Bypass Iso; SolderJumper-2_P1.3mm_Open_Pad1.0x1.5mm; PartId JP_SOLDER
MH1, MH2, MH3, MH4: MountingHole; MountingHole_3.2mm_M3
R1: 120; R_Axial_DIN0207_L6.3mm_D2.5mm_P10.16mm_Horizontal; PartId R_120
R2, R3, R4, R5, R6, R7: 470; R_Axial_DIN0207_L6.3mm_D2.5mm_P10.16mm_Horizontal; PartId R_470
SW1: TERM; ESWITCH_1218_SPDT; PartId SW_SLIDE_SM
U1: RFM-0505S; Converter_DCDC_Recom_RFM0505S_THT_Bypass; PartId U_0505
U2, U3, U4: 6N137; DIP-8_W7.62mm_Socket; MPN 6N137; Digi-Key_PN 160-1791-ND
U5: MAX485; DIP-8_W7.62mm_Socket; PartId U_485

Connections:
+5V: C2.1, J1.1, J1.2, R2.1, U1.2 (VIN+), U2.8 (VCC), U3.2 (A), U4.2 (A)
/DMX-DIR: J1.10, JP2.1 (A), R4.2
/DMX-RX: J1.9, JP1.1 (A), R2.2, U2.6 (VO)
/DMX-TX: J1.11, JP3.1 (A), R6.2
GND: C2.2, J1.13, J1.14, U1.1 (VIN-), U2.5 (GND)
GNDD: C3.2, C4.2, C5.2, J2.1A (P6), J2.1B (P1), J3.1A (P6), J3.1B (P1), U1.3 (VOUT-), U3.5 (GND), U4.5 (GND), U5.5 (GND)
unnamed: J2.2A (7), J2.2B (P2), J3.2A (7), J3.2B (P2), R1.1, U5.7 (B)
unnamed: J2.3, J3.3, SW1.2 (B), U5.6 (A)
unnamed: JP1.2 (B), R3.1, U5.1 (RO)
unnamed: JP2.2 (B), R5.1, U3.6 (VO), U5.2 (~RE), U5.3 (DE)
unnamed: JP3.2 (B), R7.1, U4.6 (VO), U5.4 (DI)
unnamed: R1.2, SW1.3 (C)
unnamed: R3.2, U2.3 (K)
unnamed: R4.1, U3.3 (K)
unnamed: R6.1, U4.3 (K)
VDD: C3.1, C4.1, C5.1, R5.2, R7.2, U1.4 (VOUT+), U2.2 (A), U3.8 (VCC), U4.8 (VCC), U5.8 (VCC)

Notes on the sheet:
Jump to Bypass Iso

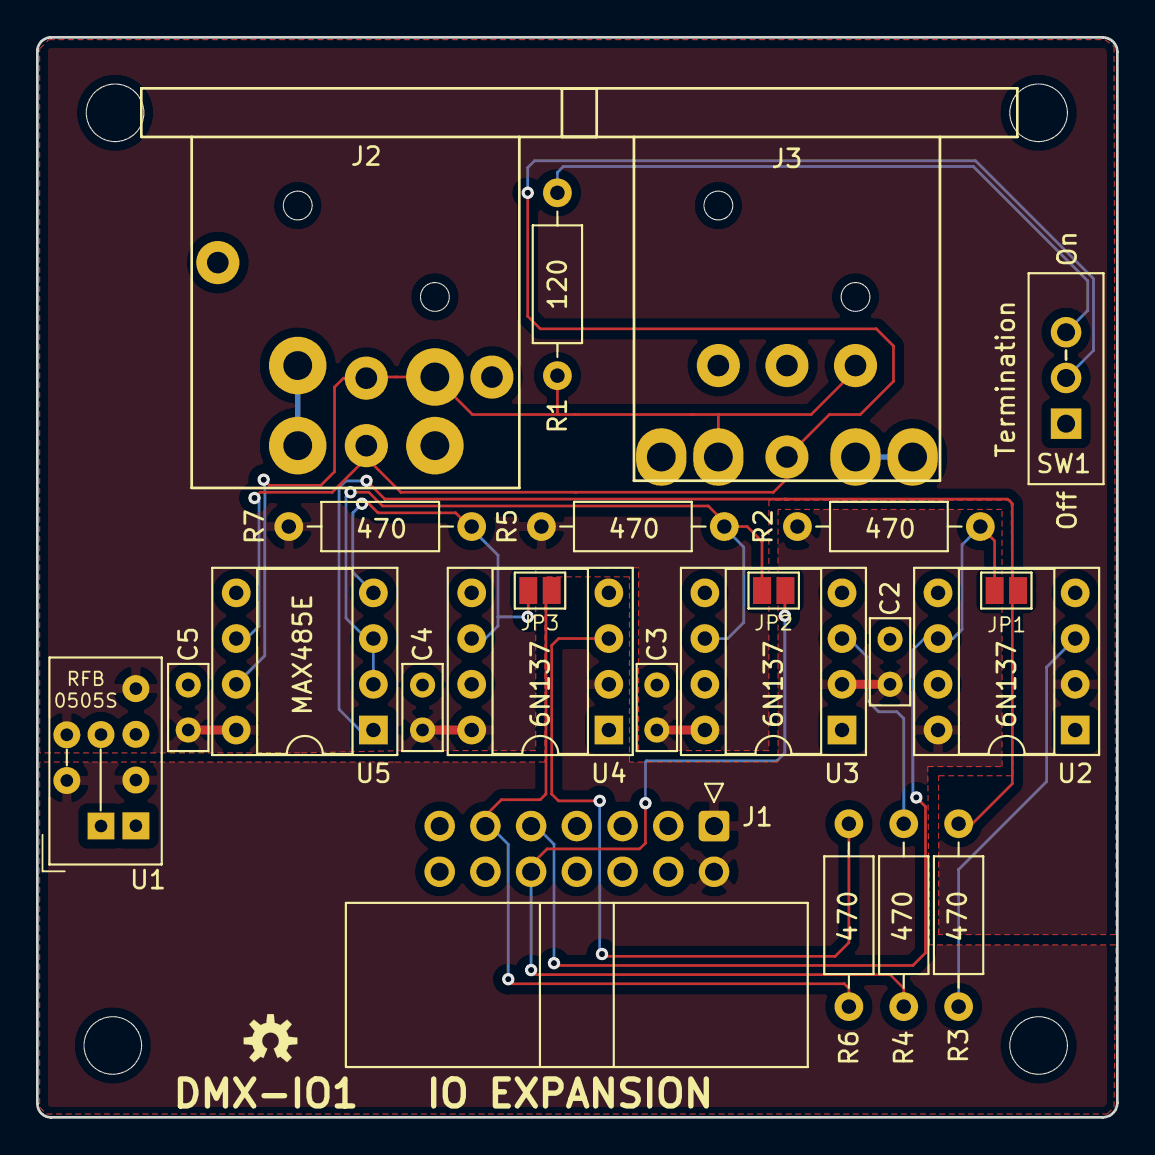
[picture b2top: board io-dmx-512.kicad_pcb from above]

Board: 2 copper layers, 60.0 x 60.0 mm, 27 parts (0 on the bottom side), 16 nets.

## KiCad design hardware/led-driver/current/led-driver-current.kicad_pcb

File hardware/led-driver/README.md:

# DMX Demonstrator Display-Pro (DMX-DSP)

## Overview

The constant voltage display driver is stand-along module which intercepts the 3-wire data/clock signal from the transmitter to amplify the data and clock signals and drive a larger display intended for a large audience.

It is built to drive an DC output for up to 60v volts so it is compatible with a variety of displays. The online parts list has a display and power supply to keep you from having to come up with your own. Feel free to use the recommended option or play around with something else.

## Online parts list

Sparkfun offers all of the components required for the constant voltage display driver. You can find a parts lists [here](https://www.sparkfun.com/wish_lists/160583).

If you plan to use something else for the display, you can leave out the Big Dome Buttons, the 12v power supply (you'll likely need something to supply more current anyway). You may also want to consider adding heat sinks, either two of the [PRT-00121](https://www.sparkfun.com/products/121) or [PRT-14340](https://www.sparkfun.com/products/14340) depending on your load.

The screw terminals are Phoenix Contact 2-Pin 3.81mm Pitch Plug-in Screw Right Angle Terminal Block Connectors. They can easily be found on Amazon. However, any 3.81 pithc connector shoudl also work, in addition to direct wire connections.

## PCB

You can order the PCB from [OHS Park](https://oshpark.com/):

- [DMX-DSP, Rev 1.5](https://oshpark.com/shared_projects/vsJuLlDO).

## Version History

### Rev 1.5

- Switch to smaller screw terminal connectors
- Add pull-down resistors
- Add silkscreen values
- Remove COAX power connector...again.

### Rev 1.4

- Refactor display-pro to work with io-analog-pwm
- Add correct COAX power connector

### Rev 1.3

- Standard board to match IO modules

### Rev 1.2

- Remove COAX power connector

### Rev 1.1

- Added rounded corners

### Rev 1.0

- Initial draft

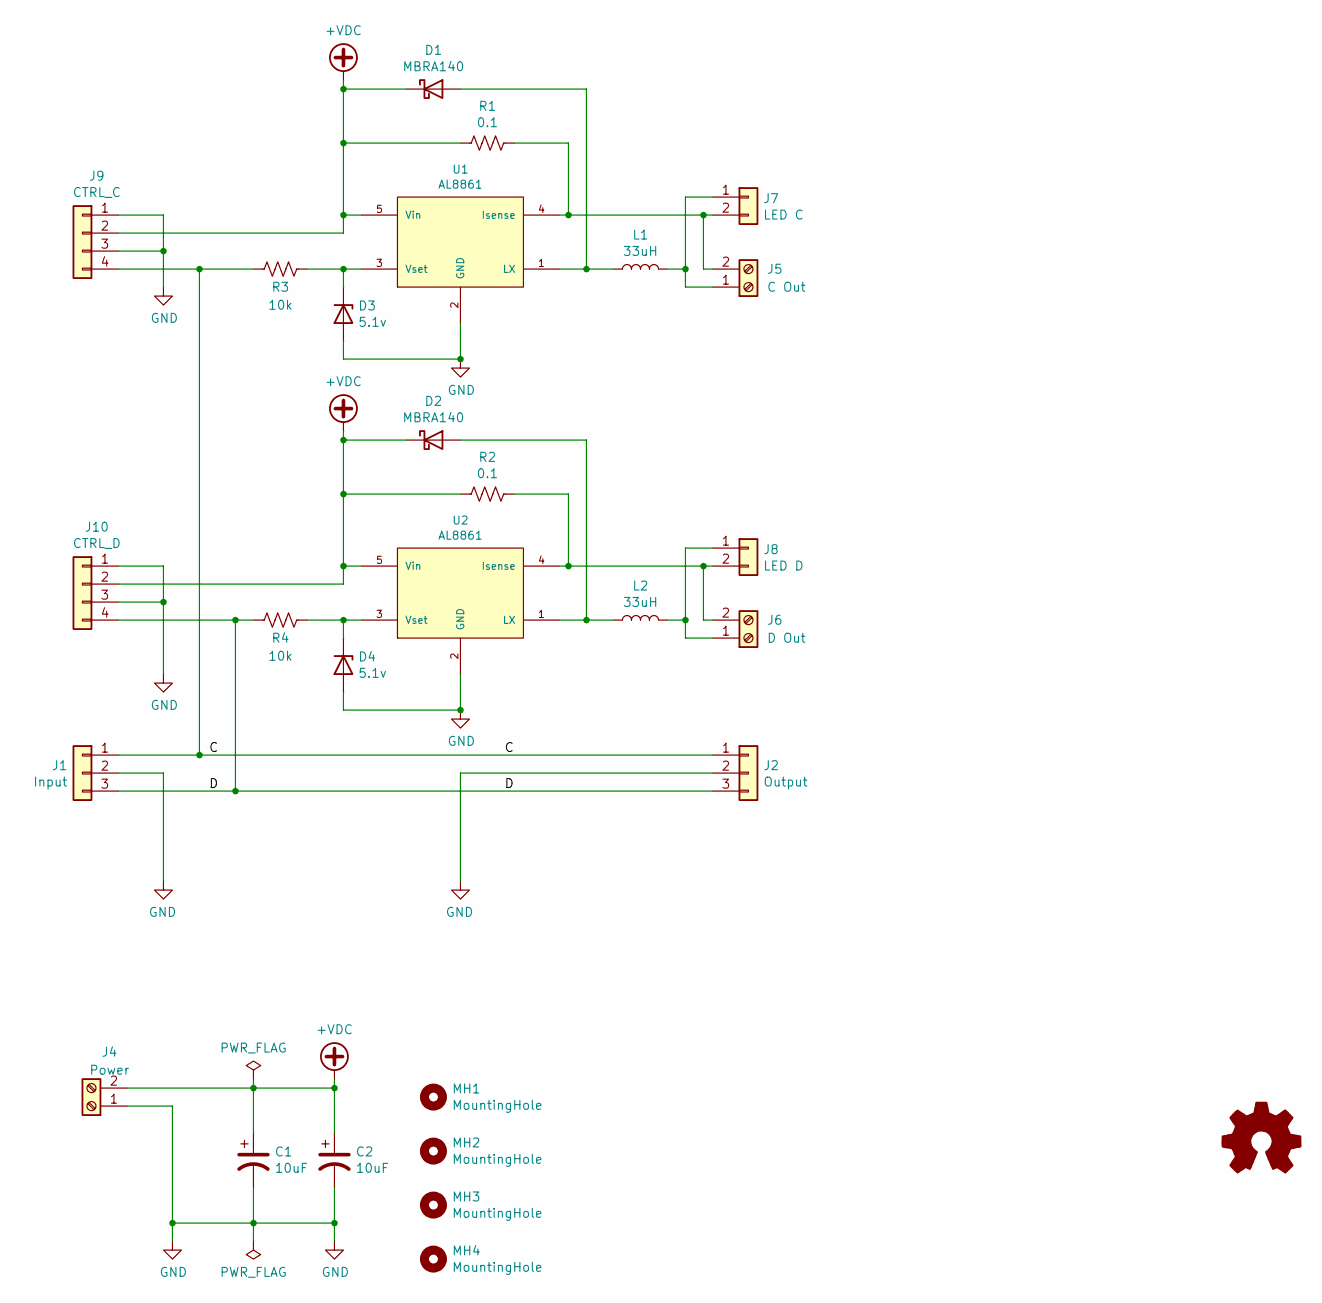
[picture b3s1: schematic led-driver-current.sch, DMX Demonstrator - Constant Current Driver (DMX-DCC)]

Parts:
C1, C2: 10uF; C_1206_3216Metric_Pad1.42x1.75mm_HandSolder; PartId C_FILTER_SMD
D1, D2: MBRA140; D_SMA_Handsoldering; PartId D_FLYBACK_SMD
D3, D4: 5.1v; D_SMA_Handsoldering; PartId ZD_5v1_SMD
J1: Input; PinHeader_1x03_P2.54mm_Horizontal; PartId H_1x3_RA,JP_1x3
J2: Output; PinHeader_1x03_P2.54mm_Horizontal; PartId H_1x3_RA
J4: Power; PhoenixContact_MC_1,5_2-G-3.81_1x02_P3.81mm_Horizontal; PartId J-381x2,P-381x2
J5: C Out; PhoenixContact_MC_1,5_2-G-3.81_1x02_P3.81mm_Horizontal; PartId J-381x2,P-381x2
J6: D Out; PhoenixContact_MC_1,5_2-G-3.81_1x02_P3.81mm_Horizontal; PartId J-381x2,P-381x2
J7: LED C; PinHeader_1x02_P2.54mm_Vertical
J8: LED D; PinHeader_1x02_P2.54mm_Vertical
J9: CTRL_C; PinHeader_1x04_P2.54mm_Vertical
J10: CTRL_D; PinHeader_1x04_P2.54mm_Vertical
L1, L2: 33uH; L_BOURNS_SRN6045TA; PartId L_33u_SMD
MH1, MH2, MH3, MH4: MountingHole; MountingHole_3.2mm_M3
R1, R2: 0.1; R_1206_3216Metric_Pad1.42x1.75mm_HandSolder; PartId R_CC_SMD
R3, R4: 10k; R_1206_3216Metric_Pad1.42x1.75mm_HandSolder; PartId R_10k_SMD
U1, U2: AL8861; SOT-89-5_Handsoldering; PartId U_8861,MOD_8861

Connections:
+VDC: C1.1, C2.1, D1.1 (K), D2.1 (K), J4.2, J9.2, J10.2, R1.2, R2.2, U1.5 (Vin), U2.5 (Vin)
/C: J1.1, J2.1, J9.4, R3.2
/D: J1.3, J2.3, J10.4, R4.2
GND: C1.2, C2.2, D3.2 (A), D4.2 (A), J1.2, J2.2, J4.1, J9.1, J9.3, J10.1, J10.3, U1.2 (GND), U2.2 (GND)
unnamed: D1.2 (A), L1.1, U1.1 (LX)
unnamed: D2.2 (A), L2.1, U2.1 (LX)
unnamed: D3.1 (K), R3.1, U1.3 (Vset)
unnamed: D4.1 (K), R4.1, U2.3 (Vset)
unnamed: J5.1, J7.1, L1.2
unnamed: J5.2, J7.2, R1.1, U1.4 (Isense)
unnamed: J6.1, J8.1, L2.2
unnamed: J6.2, J8.2, R2.1, U2.4 (Isense)

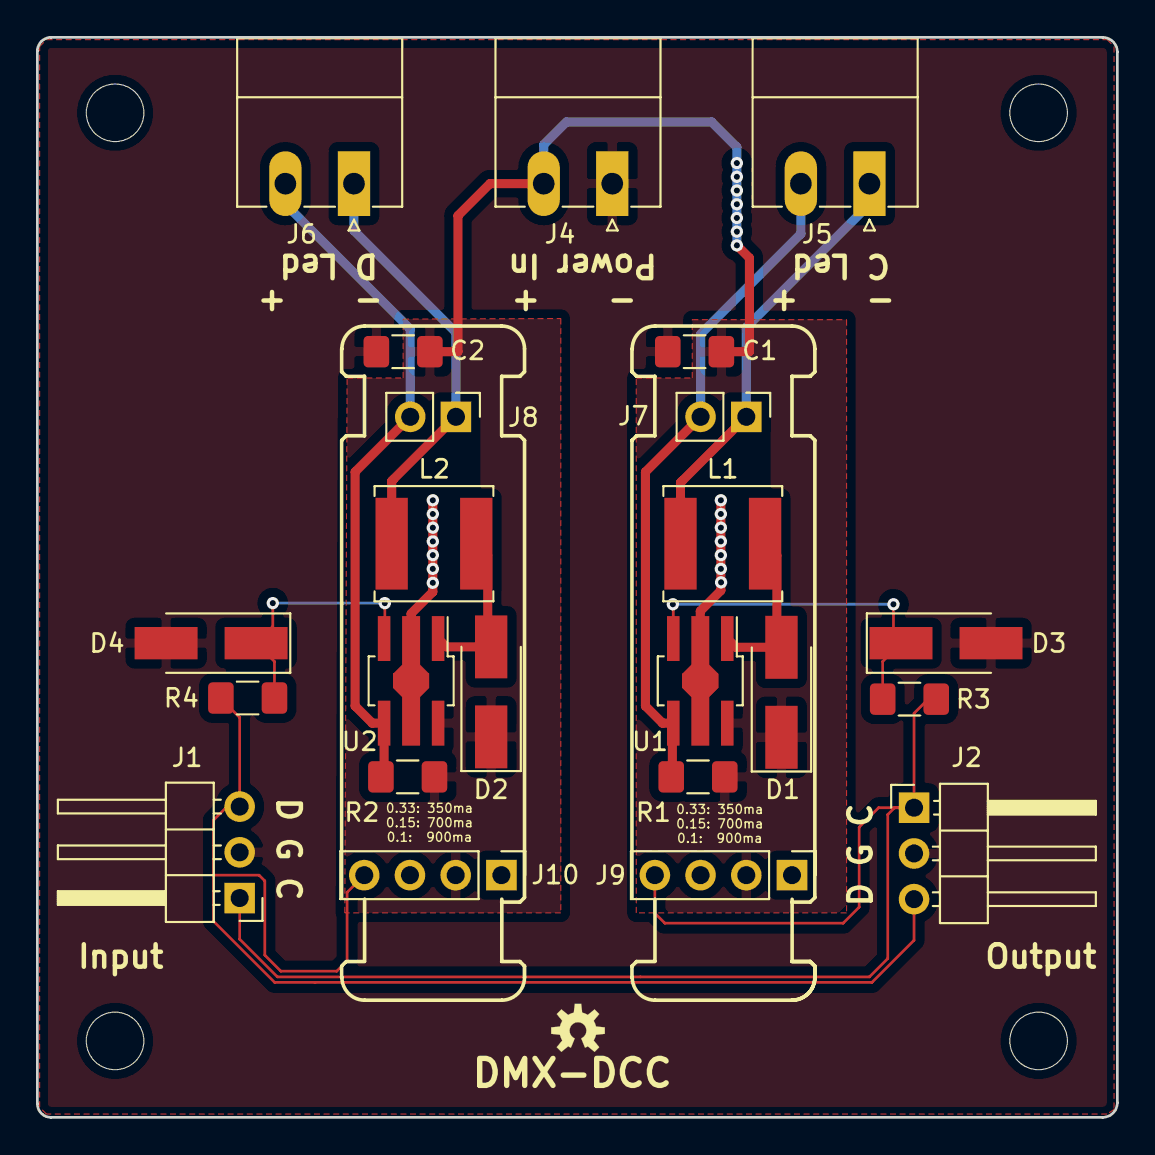
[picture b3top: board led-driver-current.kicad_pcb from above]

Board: 2 copper layers, 60.0 x 60.0 mm, 27 parts (0 on the bottom side), 12 nets.

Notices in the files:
hardware/control-pro/transmitter-adapter/transmitter-adapter.kicad_pcb:
https://creativecommons.org/licenses/by-sa/4.0
Released under the Creative Commons Attribution Share-Alike 4.0 License
hardware/io-analog/pwm/io-analog-pwm.kicad_pcb:
Released under the Creative Commons Attribution Share-Alike 4.0m License
